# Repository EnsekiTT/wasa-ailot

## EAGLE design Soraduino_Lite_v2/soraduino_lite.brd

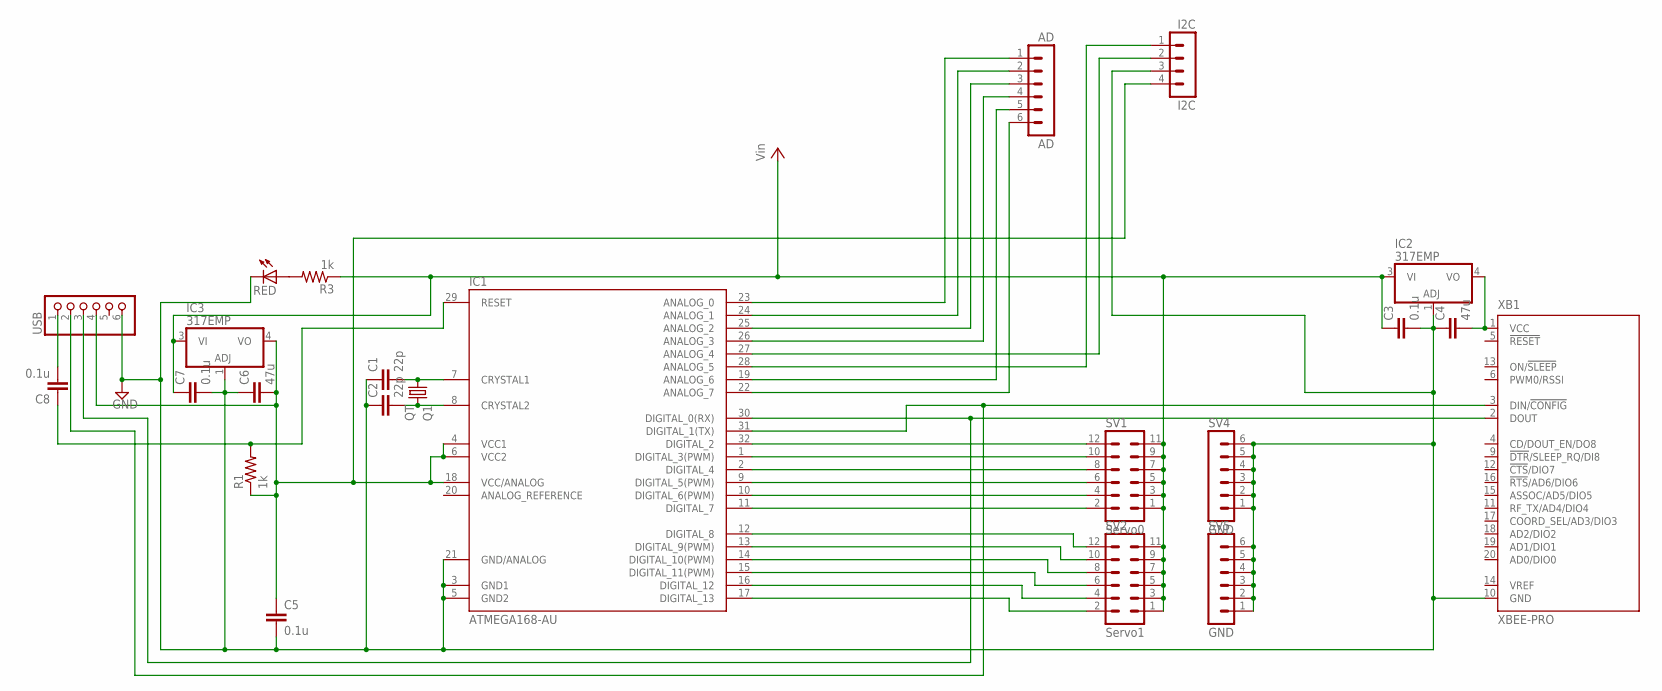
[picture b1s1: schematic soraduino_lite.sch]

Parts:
AD: AD; MA06-1
C1, C2: 22p; C050-024X044
C3, C5, C7, C8: 0.1u; C0805K
C4, C6: 47u; C0805K
I2C: I2C; MA04-1
IC1: ATMEGA168-AU; TQFP32-08
IC2, IC3: 317EMP; SOT223
Q1: QT; HC49/S
R1, R3: 1k; R0603
RED: LEDCHIPLED_1206; CHIPLED_1206
SV1: Servo0; MA06-2
SV2: Servo1; MA06-2
SV4, SV5: GND; MA06-1
USB: PINHD-1X6; 1X06
XB1: XBEE-PRO

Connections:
GND: C1.1, C2.1, C3.2, C4.1, C5.2, C6.1, C7.2, I2C.3, IC1.3 (GND1), IC1.5 (GND2), IC1.21 (GND/ANALOG), IC2.1 (ADJ), IC3.1 (ADJ), RED.C, SV4.1, SV4.2, SV4.3, SV4.4, SV4.5, SV4.6, SV5.1, SV5.2, SV5.3, SV5.4, SV5.5, SV5.6, USB.6, XB1.10 (GND)
unnamed: C8.2, USB.1
unnamed: C8.1, IC1.29 (RESET), R1.2
unnamed: IC1.30 (DIGITAL_0(RX)), USB.3, XB1.2 (DOUT)
unnamed: C1.2, IC1.7 (CRYSTAL1), Q1.1
unnamed: C2.2, IC1.8 (CRYSTAL2), Q1.2
unnamed: C4.2, IC2.4 (VO), XB1.1 (VCC)
unnamed: C5.1, C6.2, I2C.4, IC1.4 (VCC1), IC1.6 (VCC2), IC1.18 (VCC/ANALOG), IC3.4 (VO), R1.1, USB.4
unnamed: IC1.32 (DIGITAL_2), SV1.12
unnamed: IC1.1 (DIGITAL_3(PWM)), SV1.10
unnamed: R3.2, RED.A
unnamed: IC1.2 (DIGITAL_4), SV1.8
unnamed: IC1.9 (DIGITAL_5(PWM)), SV1.6
unnamed: IC1.10 (DIGITAL_6(PWM)), SV1.4
unnamed: IC1.11 (DIGITAL_7), SV1.2
unnamed: IC1.12 (DIGITAL_8), SV2.12
unnamed: IC1.13 (DIGITAL_9(PWM)), SV2.10
unnamed: IC1.14 (DIGITAL_10(PWM)), SV2.8
unnamed: IC1.15 (DIGITAL_11(PWM)), SV2.6
unnamed: IC1.16 (DIGITAL_12), SV2.4
unnamed: IC1.17 (DIGITAL_13), SV2.2
unnamed: AD.6, IC1.22 (ANALOG_7)
unnamed: AD.5, IC1.19 (ANALOG_6)
unnamed: AD.4, IC1.26 (ANALOG_3)
unnamed: AD.3, IC1.25 (ANALOG_2)
unnamed: AD.2, IC1.24 (ANALOG_1)
unnamed: AD.1, IC1.23 (ANALOG_0)
unnamed: I2C.1, IC1.28 (ANALOG_5)
unnamed: I2C.2, IC1.27 (ANALOG_4)
unnamed: IC1.31 (DIGITAL_1(TX)), USB.2, XB1.3 (DIN/!CONFIG)
VCC: C3.1, C7.1, IC2.3 (VI), IC3.3 (VI), R3.1, SV1.1, SV1.3, SV1.5, SV1.7, SV1.9, SV1.11, SV2.1, SV2.3, SV2.5, SV2.7, SV2.9, SV2.11

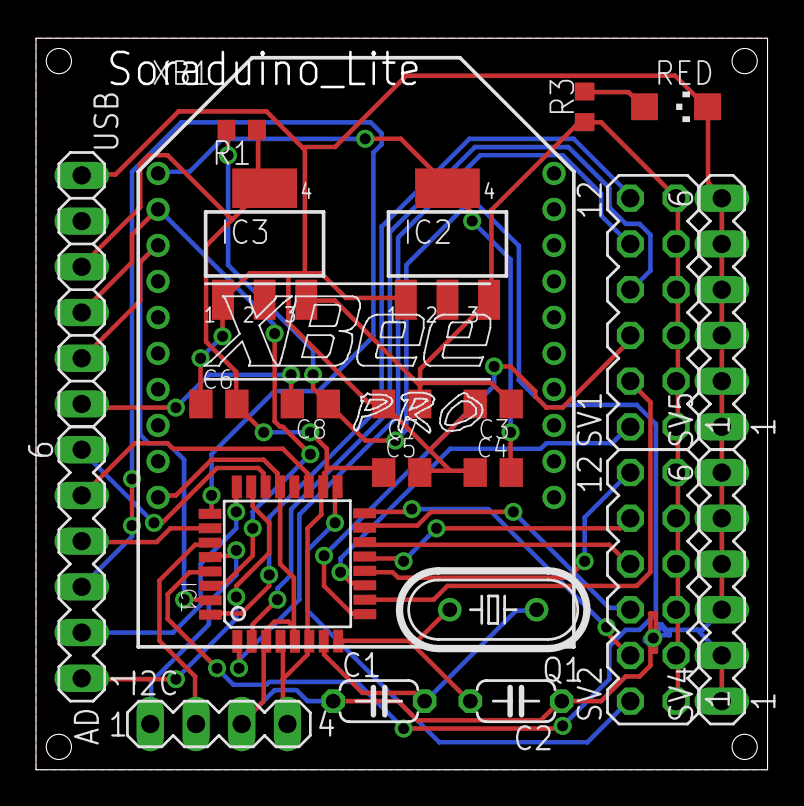
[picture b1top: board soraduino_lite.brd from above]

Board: 2 copper layers, 40.6 x 40.8 mm, 23 parts (0 on the bottom side), 31 nets.

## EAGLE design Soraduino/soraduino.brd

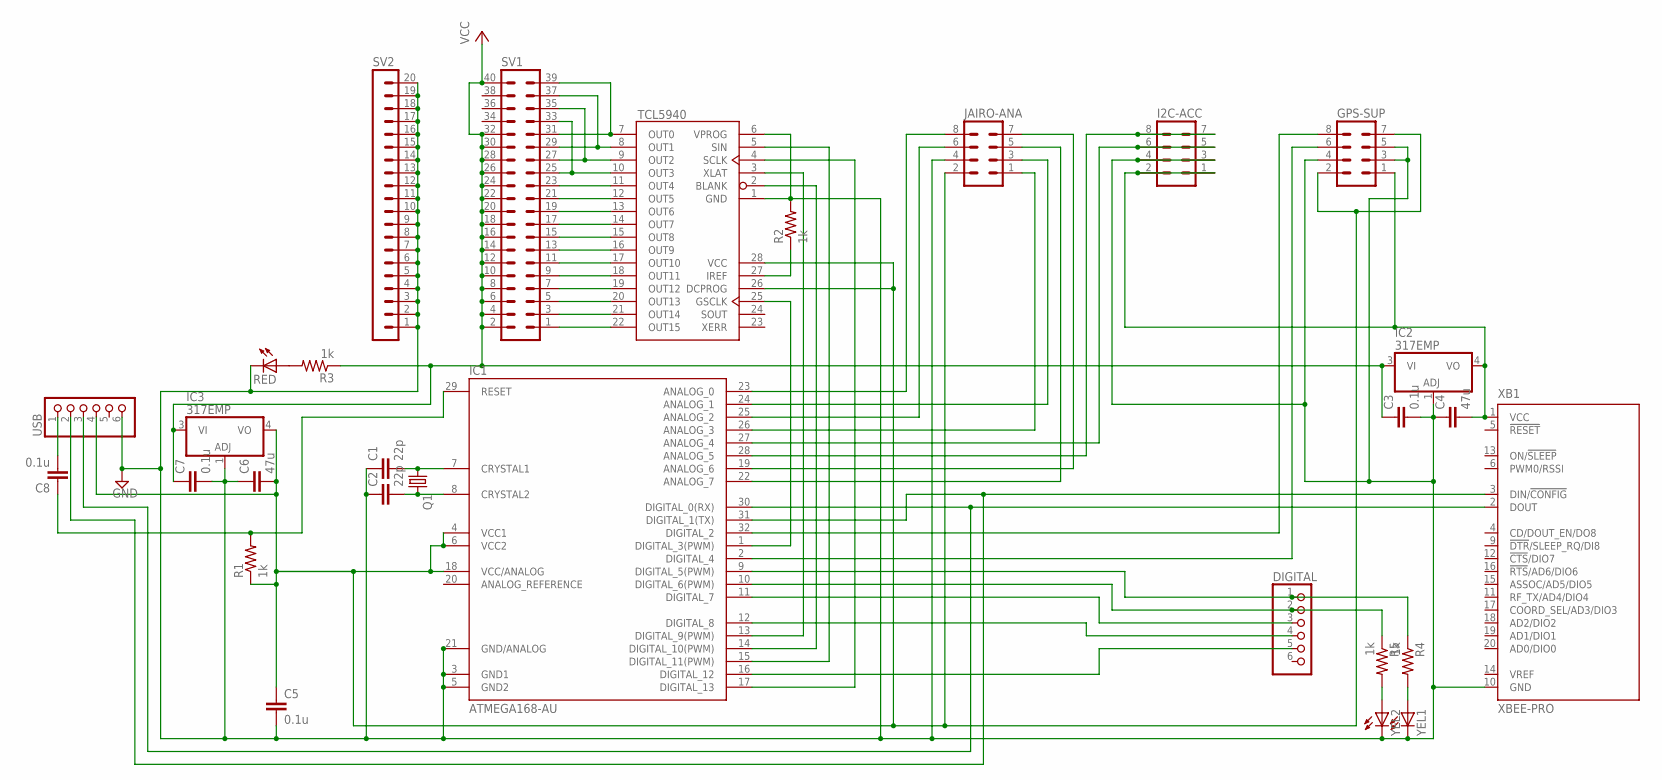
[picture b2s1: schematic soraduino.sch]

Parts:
C1, C2: 22p; C050-024X044
C3, C5, C7, C8: 0.1u; C0805K
C4, C6: 47u; C0805K
DIGITAL: PINHD-1X6; 1X06
GPS-SUP: MA04-2
I2C-ACC: MA04-2
IC1: ATMEGA168-AU; TQFP32-08
IC2, IC3: 317EMP; SOT223
IC4: TCL5940SOP; HTSSOP28PIN
JAIRO-ANA: MA04-2
Q1: CRYSTALHC49S; HC49/S
R1, R2, R3, R4, R5: 1k; R0603
RED: LEDCHIPLED_1206; CHIPLED_1206
SV1: MA20-2
SV2: MA20-1
USB: PINHD-1X6; 1X06
XB1: XBEE-PRO
YEL1, YEL2: LEDCHIPLED_1206; CHIPLED_1206

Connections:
GND: C1.1, C2.1, C3.2, C4.1, C5.2, C6.1, C7.2, GPS-SUP.3, GPS-SUP.4, GPS-SUP.5, I2C-ACC.3, I2C-ACC.4, IC1.3 (GND1), IC1.5 (GND2), IC1.21 (GND/ANALOG), IC2.1 (ADJ), IC3.1 (ADJ), IC4.1 (GND), IC4.6 (VPROG), JAIRO-ANA.4, R2.2, RED.C, SV2.1, SV2.2, SV2.3, SV2.4, SV2.5, SV2.6, SV2.7, SV2.8, SV2.9, SV2.10, SV2.11, SV2.12, SV2.13, SV2.14, SV2.15, SV2.16, SV2.17, SV2.18, SV2.19, SV2.20, USB.6, XB1.10 (GND), YEL1.C, YEL2.C
unnamed: C8.2, USB.1
unnamed: C8.1, IC1.29 (RESET), R1.2
unnamed: IC1.30 (DIGITAL_0(RX)), USB.3, XB1.2 (DOUT)
unnamed: C1.2, IC1.7 (CRYSTAL1), Q1.1
unnamed: C2.2, IC1.8 (CRYSTAL2), Q1.2
unnamed: C4.2, GPS-SUP.1, I2C-ACC.1, I2C-ACC.2, IC2.4 (VO), XB1.1 (VCC)
unnamed: C5.1, C6.2, GPS-SUP.2, GPS-SUP.7, IC1.4 (VCC1), IC1.6 (VCC2), IC1.18 (VCC/ANALOG), IC3.4 (VO), IC4.26 (DCPROG), IC4.28 (VCC), JAIRO-ANA.2, R1.1, USB.4
unnamed: IC4.8 (OUT1), SV1.29, SV1.37
unnamed: IC4.7 (OUT0), SV1.31, SV1.39
unnamed: R3.2, RED.A
unnamed: IC4.9 (OUT2), SV1.27, SV1.35
unnamed: IC4.10 (OUT3), SV1.25, SV1.33
unnamed: IC4.11 (OUT4), SV1.23
unnamed: IC4.12 (OUT5), SV1.21
unnamed: IC4.13 (OUT6), SV1.19
unnamed: IC4.14 (OUT7), SV1.17
unnamed: IC4.15 (OUT8), SV1.15
unnamed: IC4.16 (OUT9), SV1.13
unnamed: IC4.17 (OUT10), SV1.11
unnamed: IC4.18 (OUT11), SV1.9
unnamed: IC4.19 (OUT12), SV1.7
unnamed: IC4.20 (OUT13), SV1.5
unnamed: IC4.21 (OUT14), SV1.3
unnamed: IC4.22 (OUT15), SV1.1
unnamed: IC1.25 (ANALOG_2), JAIRO-ANA.6
unnamed: IC1.1 (DIGITAL_3(PWM)), IC4.25 (GSCLK)
unnamed: IC1.13 (DIGITAL_9(PWM)), IC4.3 (XLAT)
unnamed: IC1.14 (DIGITAL_10(PWM)), IC4.2 (BLANK)
unnamed: IC1.15 (DIGITAL_11(PWM)), IC4.5 (SIN)
unnamed: IC1.17 (DIGITAL_13), IC4.4 (SCLK)
unnamed: I2C-ACC.7, I2C-ACC.8, IC1.28 (ANALOG_5)
unnamed: I2C-ACC.5, I2C-ACC.6, IC1.27 (ANALOG_4)
unnamed: IC1.31 (DIGITAL_1(TX)), USB.2, XB1.3 (DIN/!CONFIG)
unnamed: IC1.23 (ANALOG_0), JAIRO-ANA.8
unnamed: IC1.24 (ANALOG_1), JAIRO-ANA.3
unnamed: GPS-SUP.8, IC1.32 (DIGITAL_2)
unnamed: GPS-SUP.6, IC1.2 (DIGITAL_4)
unnamed: IC4.27 (IREF), R2.1
unnamed: DIGITAL.1, IC1.9 (DIGITAL_5(PWM)), R4.1
unnamed: DIGITAL.2, IC1.10 (DIGITAL_6(PWM)), R5.1
unnamed: DIGITAL.3, IC1.11 (DIGITAL_7)
unnamed: DIGITAL.4, IC1.12 (DIGITAL_8)
unnamed: IC1.26 (ANALOG_3), JAIRO-ANA.1
unnamed: IC1.19 (ANALOG_6), JAIRO-ANA.7
unnamed: IC1.22 (ANALOG_7), JAIRO-ANA.5
unnamed: R4.2, YEL1.A
unnamed: DIGITAL.5, IC1.16 (DIGITAL_12)
unnamed: R5.2, YEL2.A
VCC: C3.1, C7.1, IC2.3 (VI), IC3.3 (VI), R3.1, SV1.2, SV1.4, SV1.6, SV1.8, SV1.10, SV1.12, SV1.14, SV1.16, SV1.18, SV1.20, SV1.22, SV1.24, SV1.26, SV1.28, SV1.30, SV1.32, SV1.40

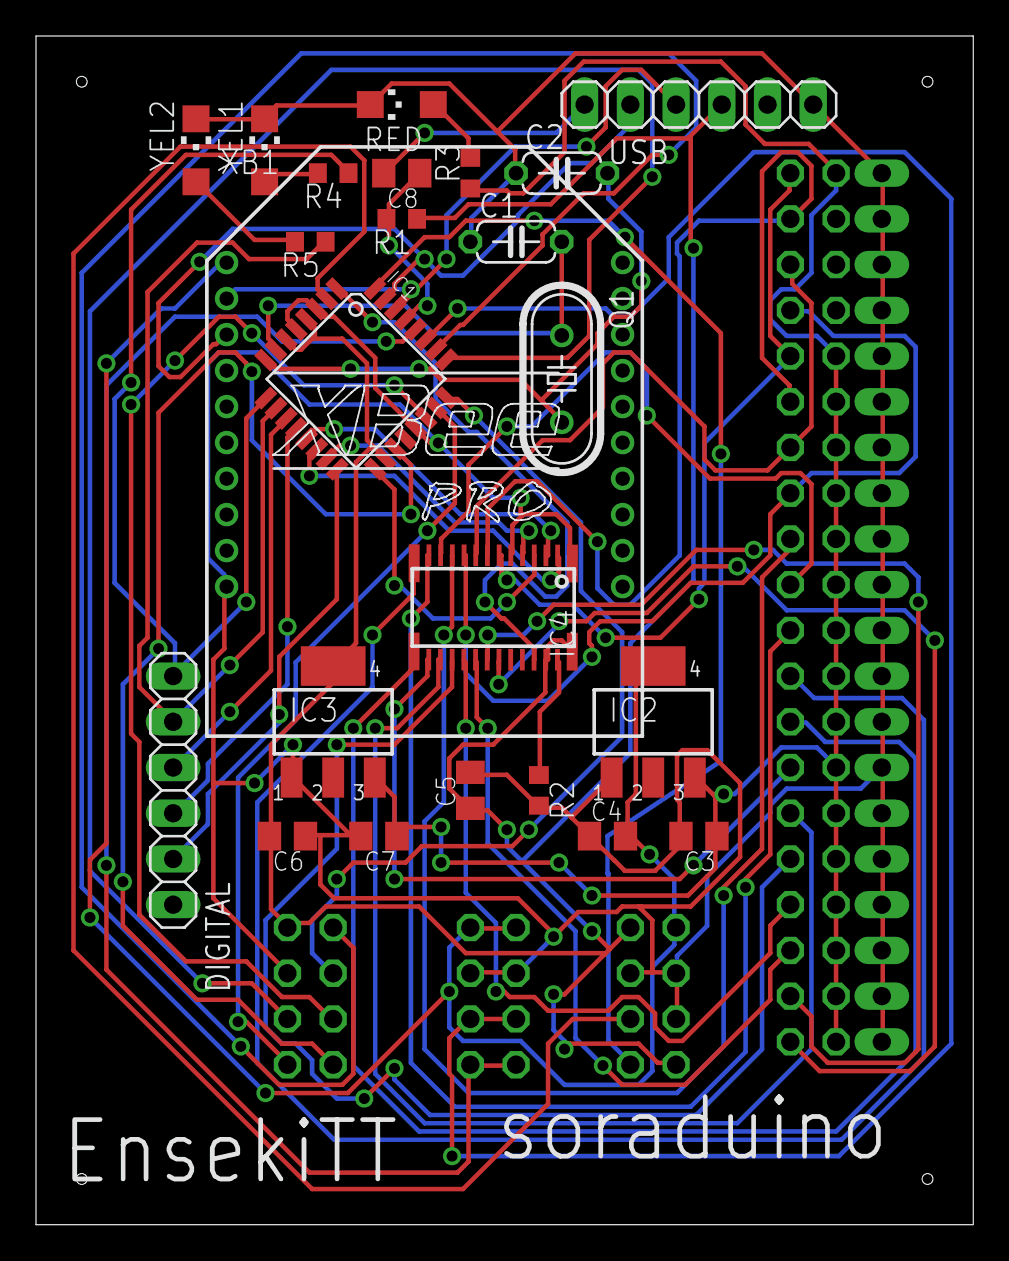
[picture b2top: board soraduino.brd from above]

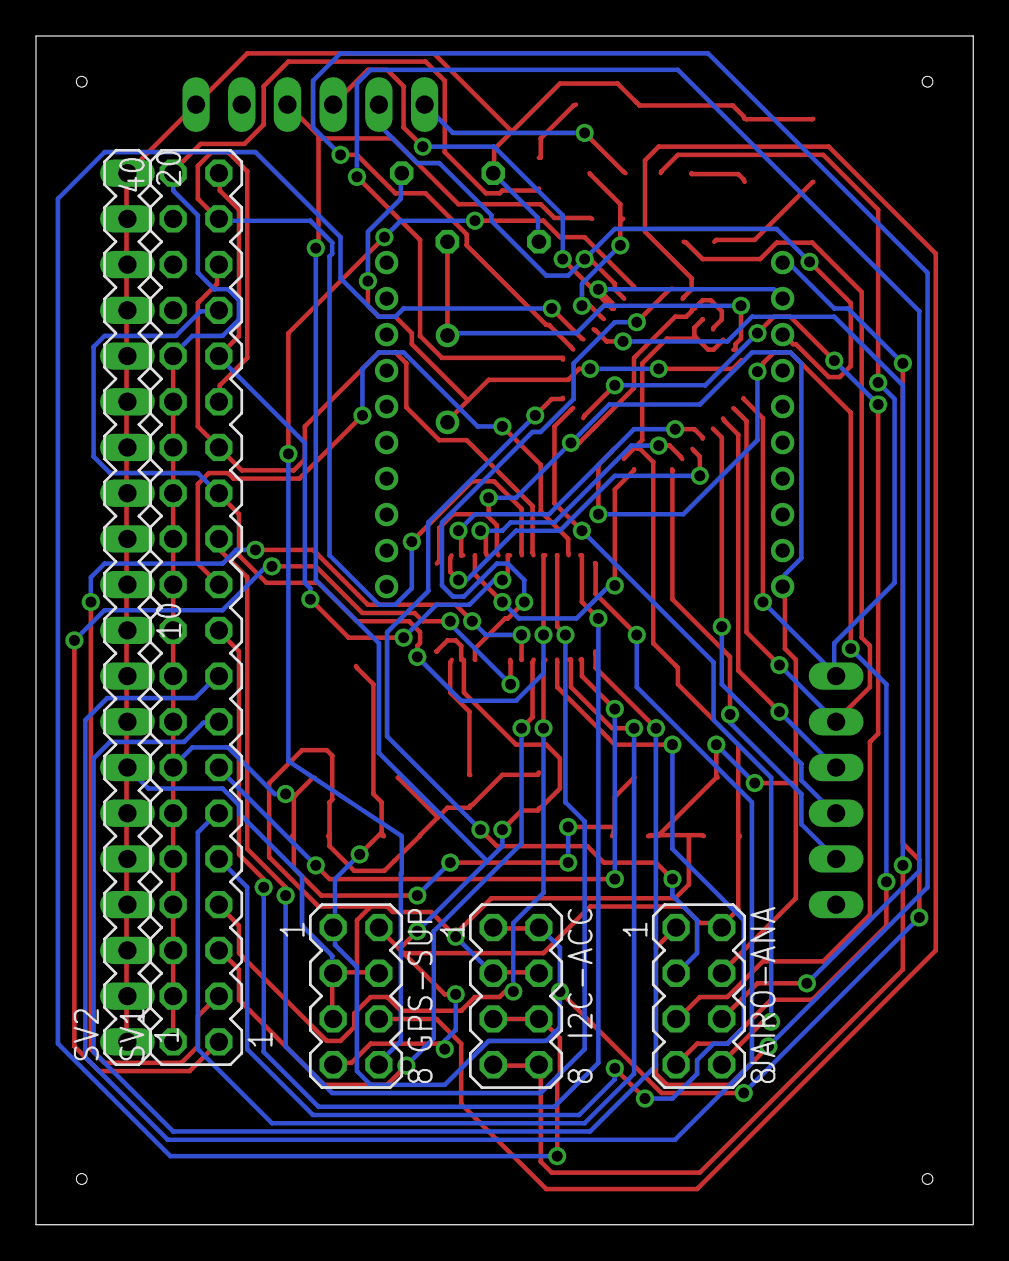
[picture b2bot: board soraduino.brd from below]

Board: 2 copper layers, 52.1 x 66.0 mm, 29 parts (5 on the bottom side), 50 nets.

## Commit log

2012-07-13 add joystick code
2012-07-13 sample compiled
2012-07-22 Arduinoにエコーバックさせるコードを追加
2012-07-22 ailot_slaveのソースファイル作成
2012-07-22 サーボ動作とセンサのライブラリ導入、センサ実験は未だ
2012-07-23 角加速度取得完了
2012-08-03 crystal設置
2012-08-07 回路の接続のみ完了
2012-08-07 GPS、Digital出力を一旦削除
2012-08-07 仮配線完了
2012-08-07 back GPS 1
2012-08-07 Revert "GPS、Digital出力を一旦削除"
    This reverts commit f31cc228a309c3dd5619f128104a36497abb7aed.
2012-08-07 回路をとりあえず完成
2012-09-09 Soraduino lite
2012-09-17 IMU_Fusion_Board and joystick
2012-09-28 PSコントローラでミミズゲーム（蛇足）
2012-09-28 soraduino_lite_v2
2012-09-29 PS3 control interface
2012-10-03 ailot_slaveの作成
2012-10-06 PS3 control beta
2012-10-08 PS3control 完了
2012-10-10 UI Sensor等々
2012-10-11 auto pilot
2012-10-11 通信安定化
2012-10-13 bagnow
2012-10-17 大会終了！飛んだ！！
